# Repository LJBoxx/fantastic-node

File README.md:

# fantastic-node
A meshtastic node designed to be self sufficient (solar powered) and small/unnoticeable enough to be planted in urban spaces.

I think that mestastic is a great project aiming at making an offgrid network of devices allowing for communication but as part of how it operates, it is limited by the cost and ease of implementing these community ran nodes transmitting packets across a city for instance. 

In this repo, you will find a pcb meant to be affordable, with a 3d printable case and easily sourcable parts.

## Schematic and PCB!

## Full CAD assembly

# BOM 
| Name     | Qty     | Price  | Link   | Note |
| -------- | ------- | ------ | ------ | ----- |
| Components | 1     | 20usd  | /hardware/bom_export_mesh.xls |
| PCB      | 1x5pcs  | 5usd | https://jlcpcb.com/ | |
|3d printed parts | 2 | 0.1usd | N/A |  Print it yourself|
| total         |         | usd |  |shipping included

# Assembly

1. Assemble the pcb put all components together and soldere them using the schematic 
2. Print the case+parts and glue the solar pannel in place then place all heat inserts in holes
3. Build the firmware following [meshtastic instructions](https://meshtastic.org/docs/development/firmware/build/) using files in /firmware/* and flash with usb !
4. Put the board and wire antenna plug connect battery to terminals to test out if working and then glue the battery and screw everything together. Use the f3d file to help with assembly :3
(will add more details and pics once i make it)

# ZINEE

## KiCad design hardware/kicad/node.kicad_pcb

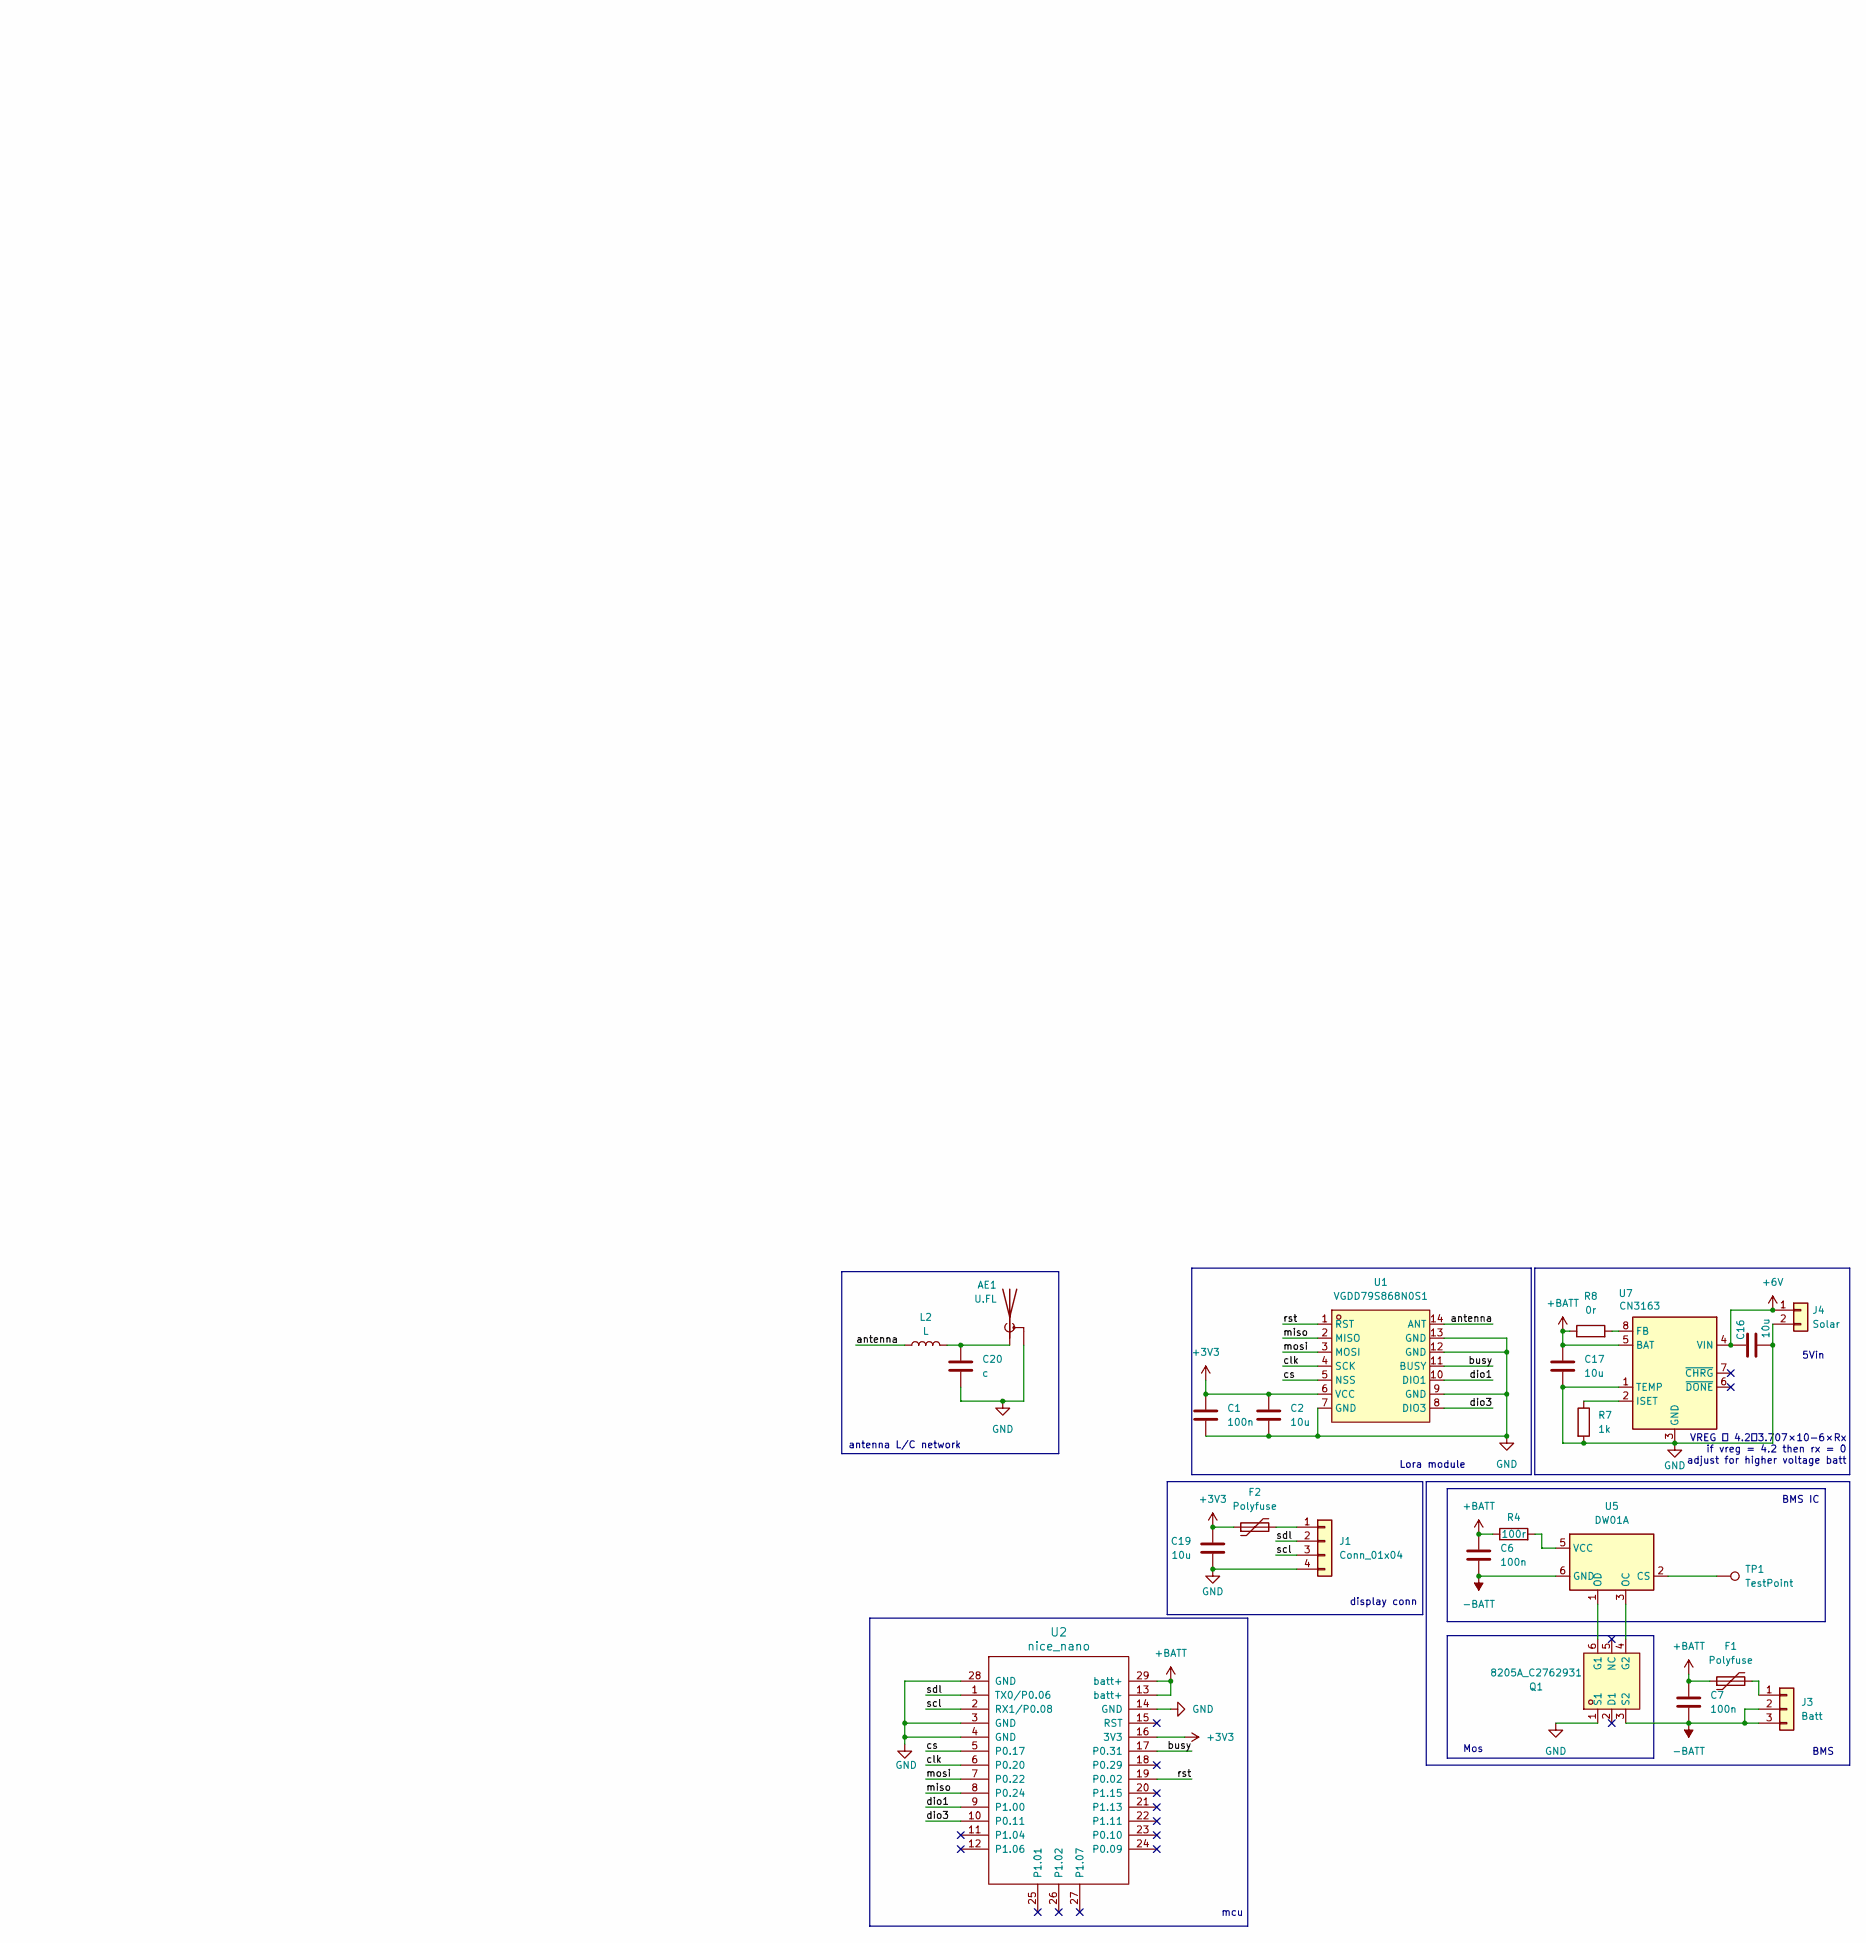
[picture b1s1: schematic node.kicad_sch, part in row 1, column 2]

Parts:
AE1: U.FL; U.FL_Hirose_U.FL-R-SMT-1_Vertical; LCSC Part C88374
C1, C6, C7: 100n; C_0603_1608Metric; LCSC Part C24497
C2, C16, C17, C19: 10u; C_0603_1608Metric; LCSC Part C962136
C20: c; C_0402_1005Metric; LCSC Part x
F1, F2: Polyfuse; Fuse_0603_1608Metric; LCSC Part C49318281
J1: Conn_01x04; PinHeader_1x04_P2.54mm_Vertical; LCSC Part x
J3: Batt; PinHeader_1x03_P2.54mm_Vertical; LCSC Part x
J4: Solar; PinHeader_1x02_P2.54mm_Vertical; LCSC Part x
L2: L; L_0402_1005Metric; LCSC Part C242160
Q1: 8205A_C2762931; SOT-23-6; LCSC Part C2762931
R4: 100r; R_0603_1608Metric; LCSC Part C105588
R7: 1k; R_0603_1608Metric; LCSC Part C7422246
R8: 0r; R_0603_1608Metric; LCSC Part x
TP1: TestPoint; TestPoint_Pad_1.5x1.5mm; LCSC Part x
U1: VGDD79S868N0S1; WIRELM-SMD_L11.5-W11.5-P1.50-BL; LCSC Part C2848400
U2: nice_nano; SuperMini NRF52840; LCSC Part x
U5: DW01A; SOT-23-6; LCSC Part C39846919
U7: CN3163; SOIC-8-1EP_3.9x4.9mm_P1.27mm_EP2.41x3.3mm_ThermalVias; LCSC Part C559031

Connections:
+3V3: C1.1, C2.1, C19.1, F2.1, U1.6 (VCC), U2.16 (3V3)
+6V: C16.1, J4.1, U7.4 (VIN)
+BATT: C6.1, C7.1, C17.1, F1.1, R4.1, R8.1, U2.13 (batt+), U2.29 (batt+), U7.5 (BAT)
-BATT: C6.2, C7.2, J3.2, J3.3, Q1.3 (S2), U5.6 (GND)
/antenna: L2.1, U1.14 (ANT)
/busy: U1.11 (BUSY), U2.17 (P0.31)
/chrg: U7.7 (~CHRG)
/clk: U1.4 (SCK), U2.6 (P0.20)
/cs: U1.5 (NSS), U2.5 (P0.17)
/dio1: U1.10 (DIO1), U2.9 (P1.00)
/dio3: U1.8 (DIO3), U2.10 (P0.11)
/miso: U1.2 (MISO), U2.8 (P0.24)
/mosi: U1.3 (MOSI), U2.7 (P0.22)
/rst: U1.1 (RST), U2.19 (P0.02)
/scl: J1.3, U2.2 (RX1/P0.08)
/sdl: J1.2, U2.1 (TX0/P0.06)
GND: AE1.2 (Shield), C1.2, C2.2, C16.2, C17.2, C19.2, C20.2, J1.4, J4.2, Q1.1 (S1), R7.2, U1.7 (GND), U1.9 (GND), U1.12 (GND), U1.13 (GND), U2.3 (GND), U2.4 (GND), U2.14 (GND), U2.28 (GND), U7.1 (TEMP), U7.3 (GND), U7.9 (GND)
unnamed: AE1.1 (A), C20.1, L2.2
unnamed: F2.2, J1.1
unnamed: F1.2, J3.1
unnamed: Q1.6 (G1), U5.1 (OD)
unnamed: Q1.4 (G2), U5.3 (OC)
unnamed: TP1.1 (1_1), U5.2 (CS)
unnamed: R4.2, U5.5 (VCC)
unnamed: R8.2, U7.8 (FB)
unnamed: R7.1, U7.2 (ISET)

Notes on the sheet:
BMS
mcu
VREG ＝ 4.2＋3.707×10-6×Rx if vreg = 4.2 then rx = 0 adjust for higher voltage batt
antenna L/C network
display conn
5Vin
BMS IC
Lora module
NRF52840
Mos

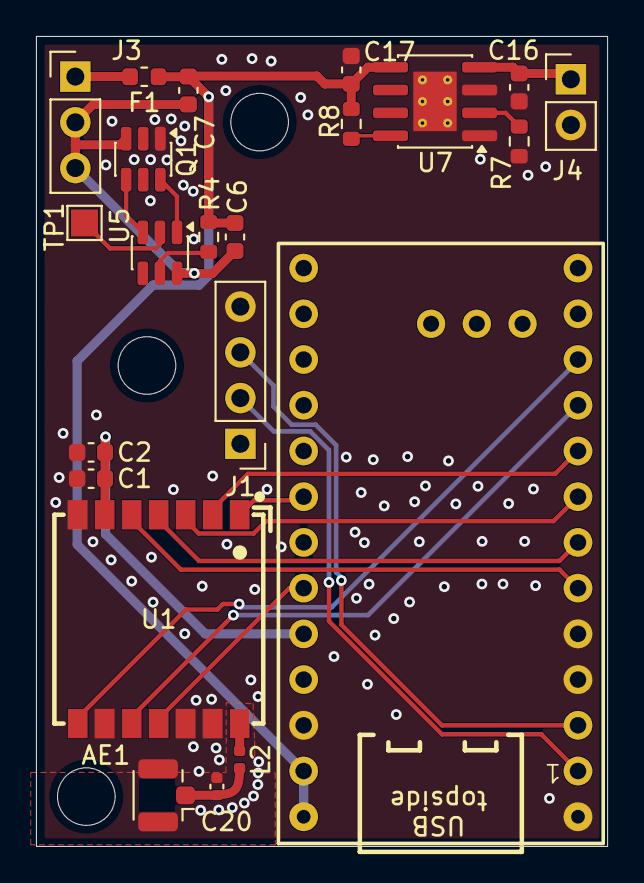
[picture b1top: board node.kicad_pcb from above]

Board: 2 copper layers, 31.7 x 45.0 mm, 22 parts (0 on the bottom side), 24 nets.

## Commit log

2026-03-21 first session, setup schematic almost finished
    next need to wire the lora module and double check everything
2026-03-22 pcbbbb placement of parts etc
2026-03-23 routing
2026-03-24 added schematic
2026-04-21 ufl antenna
2026-04-24 uuuu
2026-05-25 push before fork
2026-06-24 reorg + fixes
